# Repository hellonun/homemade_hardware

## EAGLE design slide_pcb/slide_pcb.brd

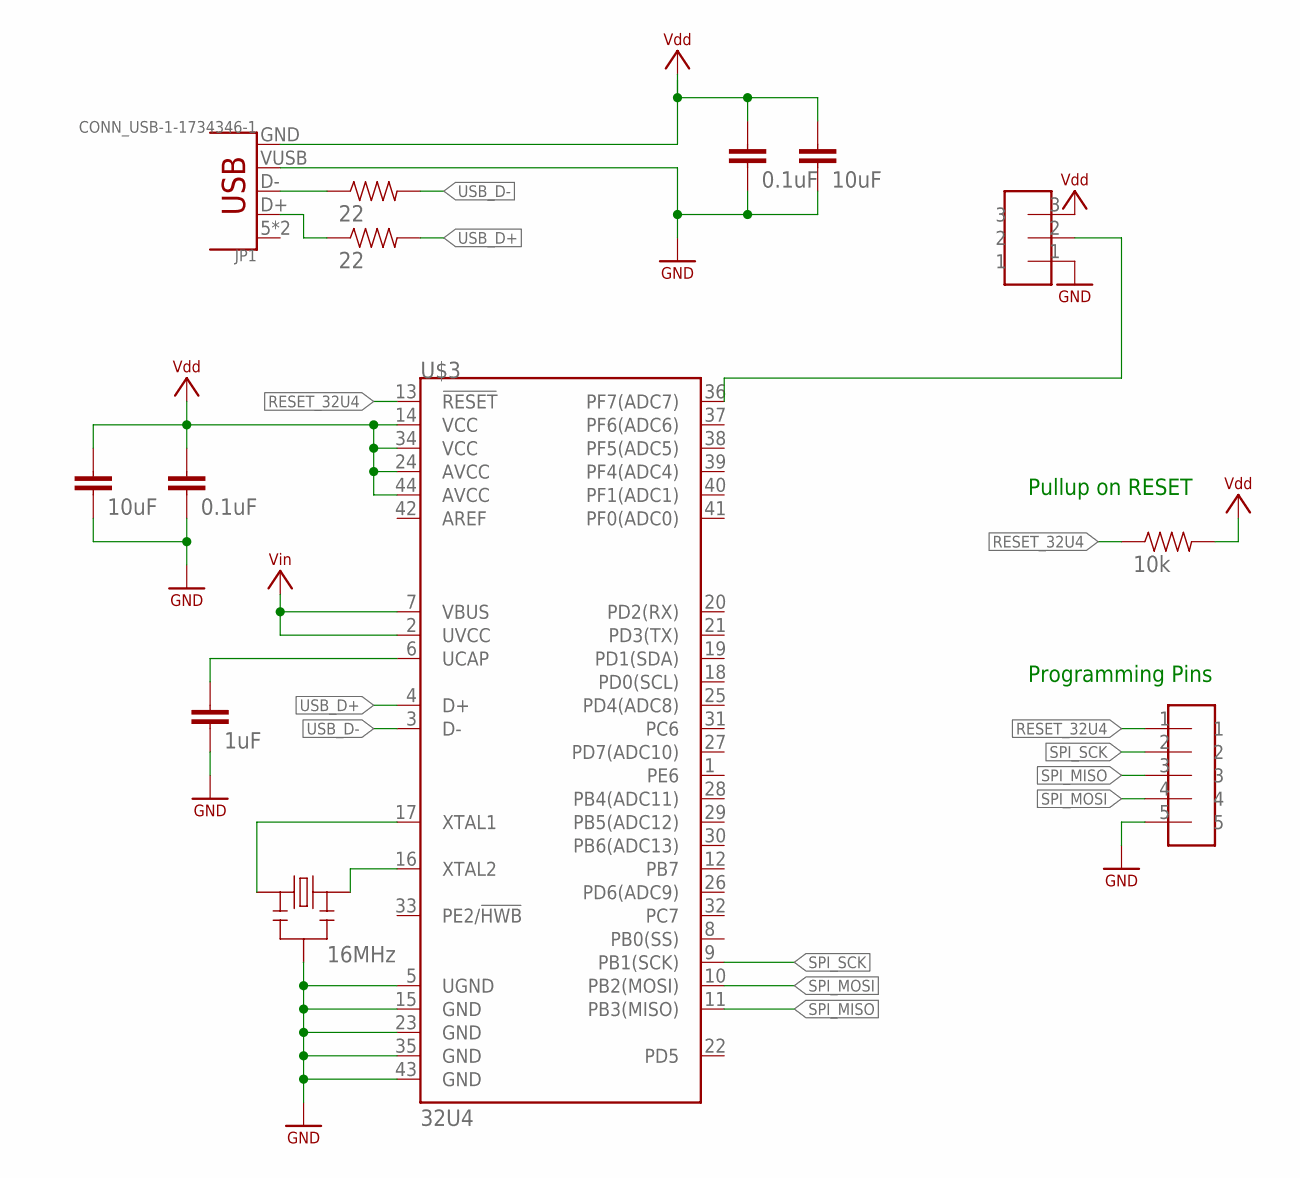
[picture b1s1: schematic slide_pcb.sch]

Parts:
C1, C6: 0.1uF; 0805
C2, C7: 10uF; 0805
C3: 1uF; 0805
JP1: CONN_USB-1-1734346-1; USB-B-SMT
R1: 10k; 0805
R4, R5: 22; 0805
U$1: HEADER-3-DIP
U$2: HEADER-5-TESTPOINT; TESTPOINT-5
U$3: 32U4; TQFP44
Y1: 16MHz; RESONATOR-SMD

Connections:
GND: C1.2, C2.2, C3.2, C6.2, C7.2, JP1.VUSB (VBUS), U$1.1, U$2.5, U$3.5 (UGND), U$3.15 (GND), U$3.23 (GND), U$3.35 (GND), U$3.43 (GND), Y1.2
unnamed: U$3.17 (XTAL1), Y1.1
unnamed: U$3.16 (XTAL2), Y1.3
unnamed: C3.1, U$3.6 (UCAP)
unnamed: JP1.D-, R5.1
unnamed: U$1.2, U$3.36 (PF7(ADC7))
unnamed: JP1.D+, R4.1
RESET_32U4: R1.1, U$2.1, U$3.13 (!RESET)
SPI_MISO: U$2.3, U$3.11 (PB3(MISO))
SPI_MOSI: U$2.4, U$3.10 (PB2(MOSI))
SPI_SCK: U$2.2, U$3.9 (PB1(SCK))
USB_D+: R4.2, U$3.4 (D+)
USB_D-: R5.2, U$3.3 (D-)
VDD: C1.1, C2.1, C6.1, C7.1, JP1.GND, R1.2, U$1.3, U$3.14 (VCC), U$3.24 (AVCC), U$3.34 (VCC), U$3.44 (AVCC)
VIN: U$3.2 (UVCC), U$3.7 (VBUS)

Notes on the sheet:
Pullup on RESET
Programming Pins

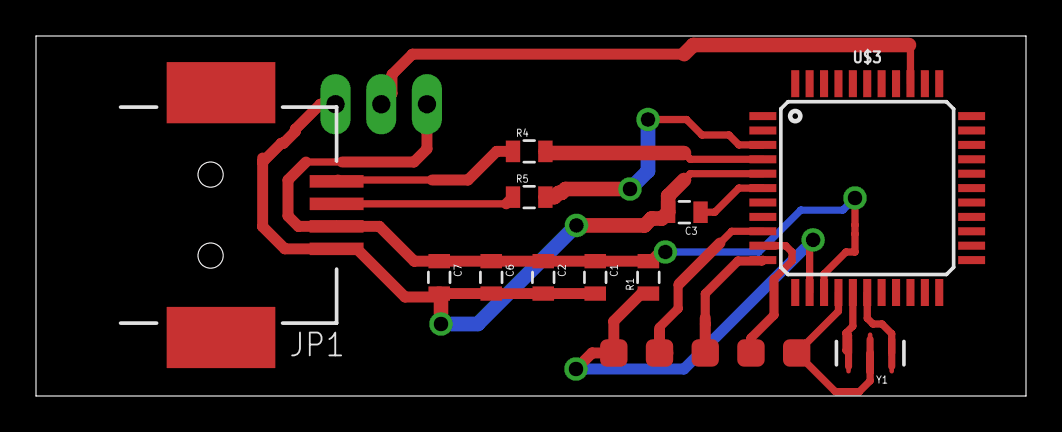
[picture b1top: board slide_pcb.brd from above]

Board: 2 copper layers, 55.0 x 20.0 mm, 13 parts (0 on the bottom side), 15 nets.

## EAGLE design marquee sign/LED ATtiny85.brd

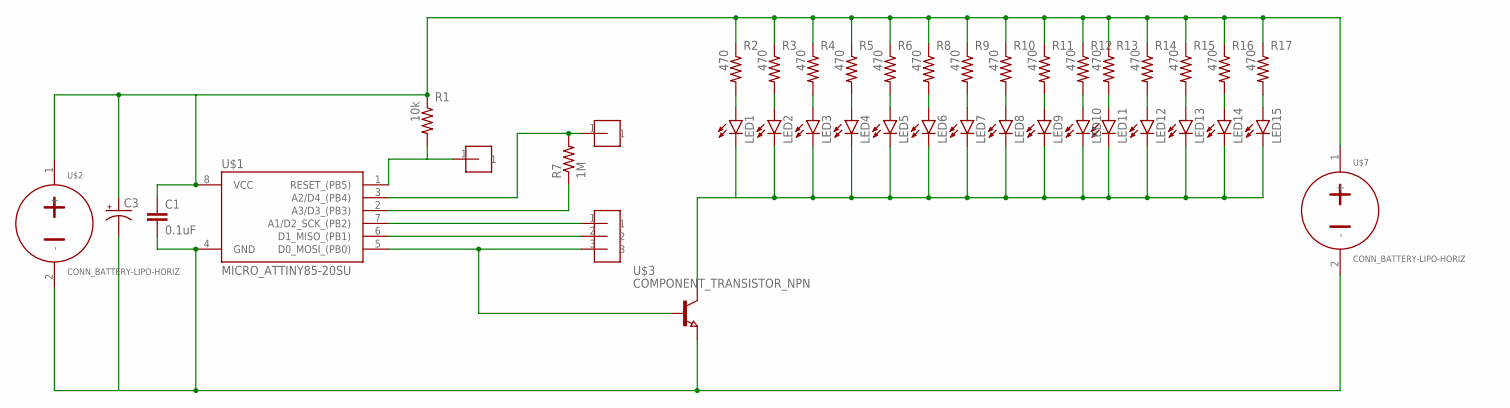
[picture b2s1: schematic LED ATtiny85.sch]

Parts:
C1: 0.1uF; 0805
C3: COMPONENT_CAP_POL-6.3MM; CAP_RADIAL_CAN_10MM
LED1, LED2, LED3, LED4, LED5, LED6, LED7, LED8, LED9, LED10, LED11, LED12, LED13, LED14, LED15: LED-0805; CHIP-LED0805
R1: 10k; 0805
R2, R3, R4, R5, R6, R8, R9, R10, R11, R12, R13, R14, R15, R16, R17: 470; 0805
R7: 1M; 0805
U$1: MICRO_ATTINY85-20SU; SOIC8
U$2, U$7: CONN_BATTERY-LIPO-HORIZ; JST-PH-2-SMT-RA
U$3: COMPONENT_TRANSISTOR_NPN; SOT23
U$4, U$5: HEADER-1-TESTPOINT; TESTPOINT-1
U$6: HEADER-3-TESTPOINT; TESTPOINT-3

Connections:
unnamed: C1.1, C3.+, R1.1, R2.1, R3.1, R4.1, R5.1, R6.1, R8.1, R9.1, R10.1, R11.1, R12.1, R13.1, R14.1, R15.1, R16.1, R17.1, U$1.8 (VCC), U$2.1 (+), U$7.1 (+)
unnamed: C1.2, C3.-, U$1.4 (GND), U$2.2 (-), U$3.2 (E), U$7.2 (-)
unnamed: R1.2, U$1.1 (RESET_(PB5)), U$5.1
unnamed: LED1.A, R2.2
unnamed: U$1.7 (A1/D2_SCK_(PB2)), U$6.1
unnamed: LED2.A, R3.2
unnamed: LED3.A, R4.2
unnamed: LED4.A, R5.2
unnamed: LED5.A, R6.2
unnamed: LED1.C, LED2.C, LED3.C, LED4.C, LED5.C, LED6.C, LED7.C, LED8.C, LED9.C, LED10.C, LED11.C, LED12.C, LED13.C, LED14.C, LED15.C, U$3.3 (C)
unnamed: R7.2, U$1.3 (A2/D4_(PB4)), U$4.1
unnamed: U$1.6 (D1_MISO_(PB1)), U$6.2
unnamed: U$1.5 (D0_MOSI_(PB0)), U$3.1 (B), U$6.3
unnamed: R7.1, U$1.2 (A3/D3_(PB3))
unnamed: LED14.A, R16.2
unnamed: LED13.A, R15.2
unnamed: LED12.A, R14.2
unnamed: LED11.A, R13.2
unnamed: LED10.A, R12.2
unnamed: LED9.A, R11.2
unnamed: LED8.A, R10.2
unnamed: LED7.A, R9.2
unnamed: LED6.A, R8.2
unnamed: LED15.A, R17.2

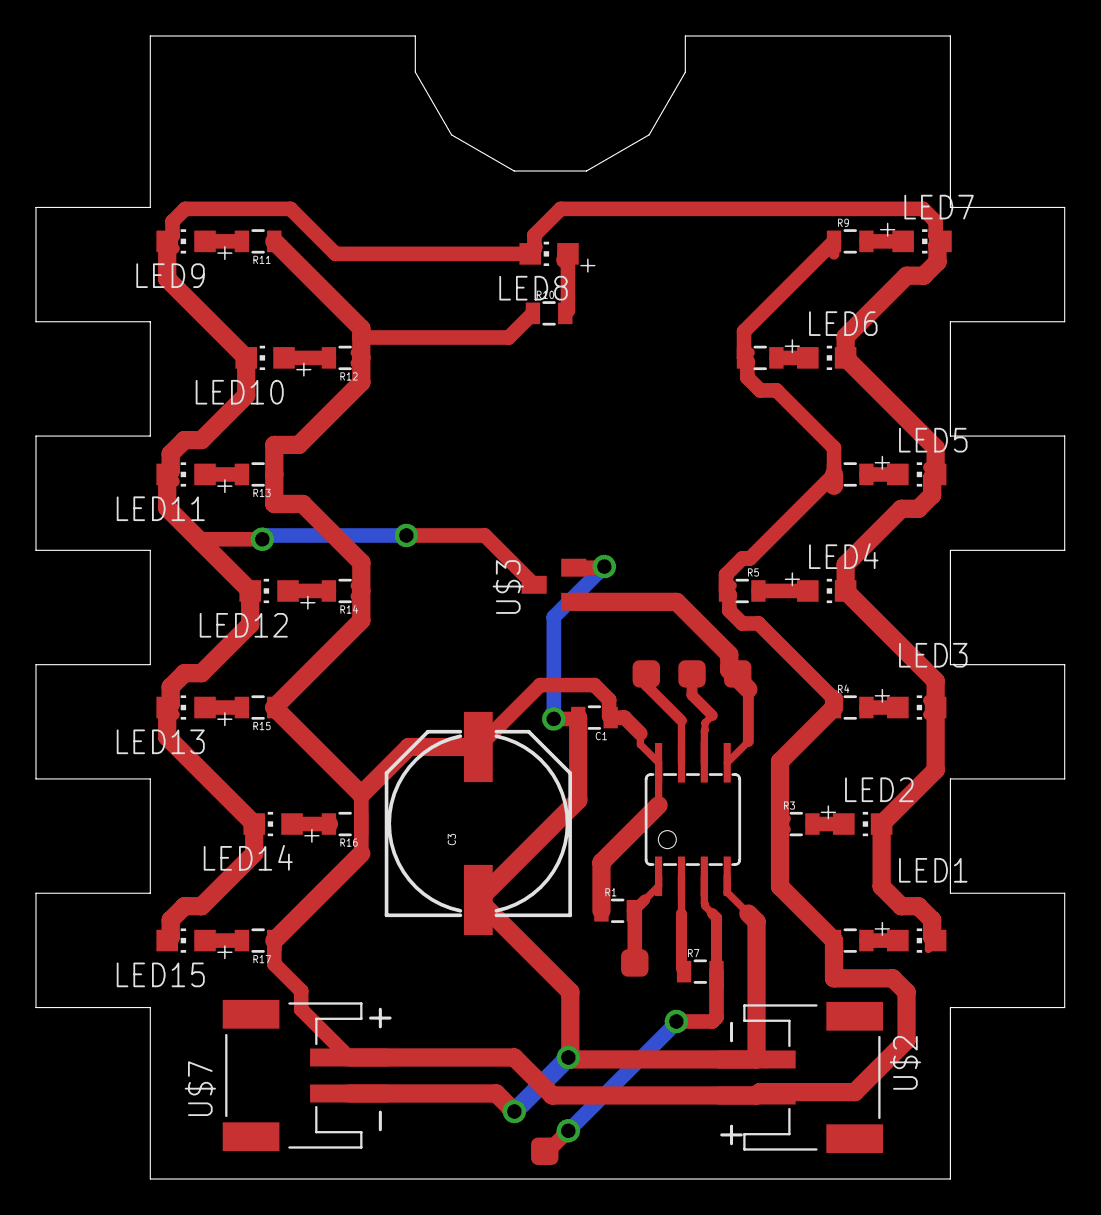
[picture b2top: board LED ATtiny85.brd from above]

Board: 2 copper layers, 57.2 x 63.5 mm, 41 parts (0 on the bottom side), 24 nets.
